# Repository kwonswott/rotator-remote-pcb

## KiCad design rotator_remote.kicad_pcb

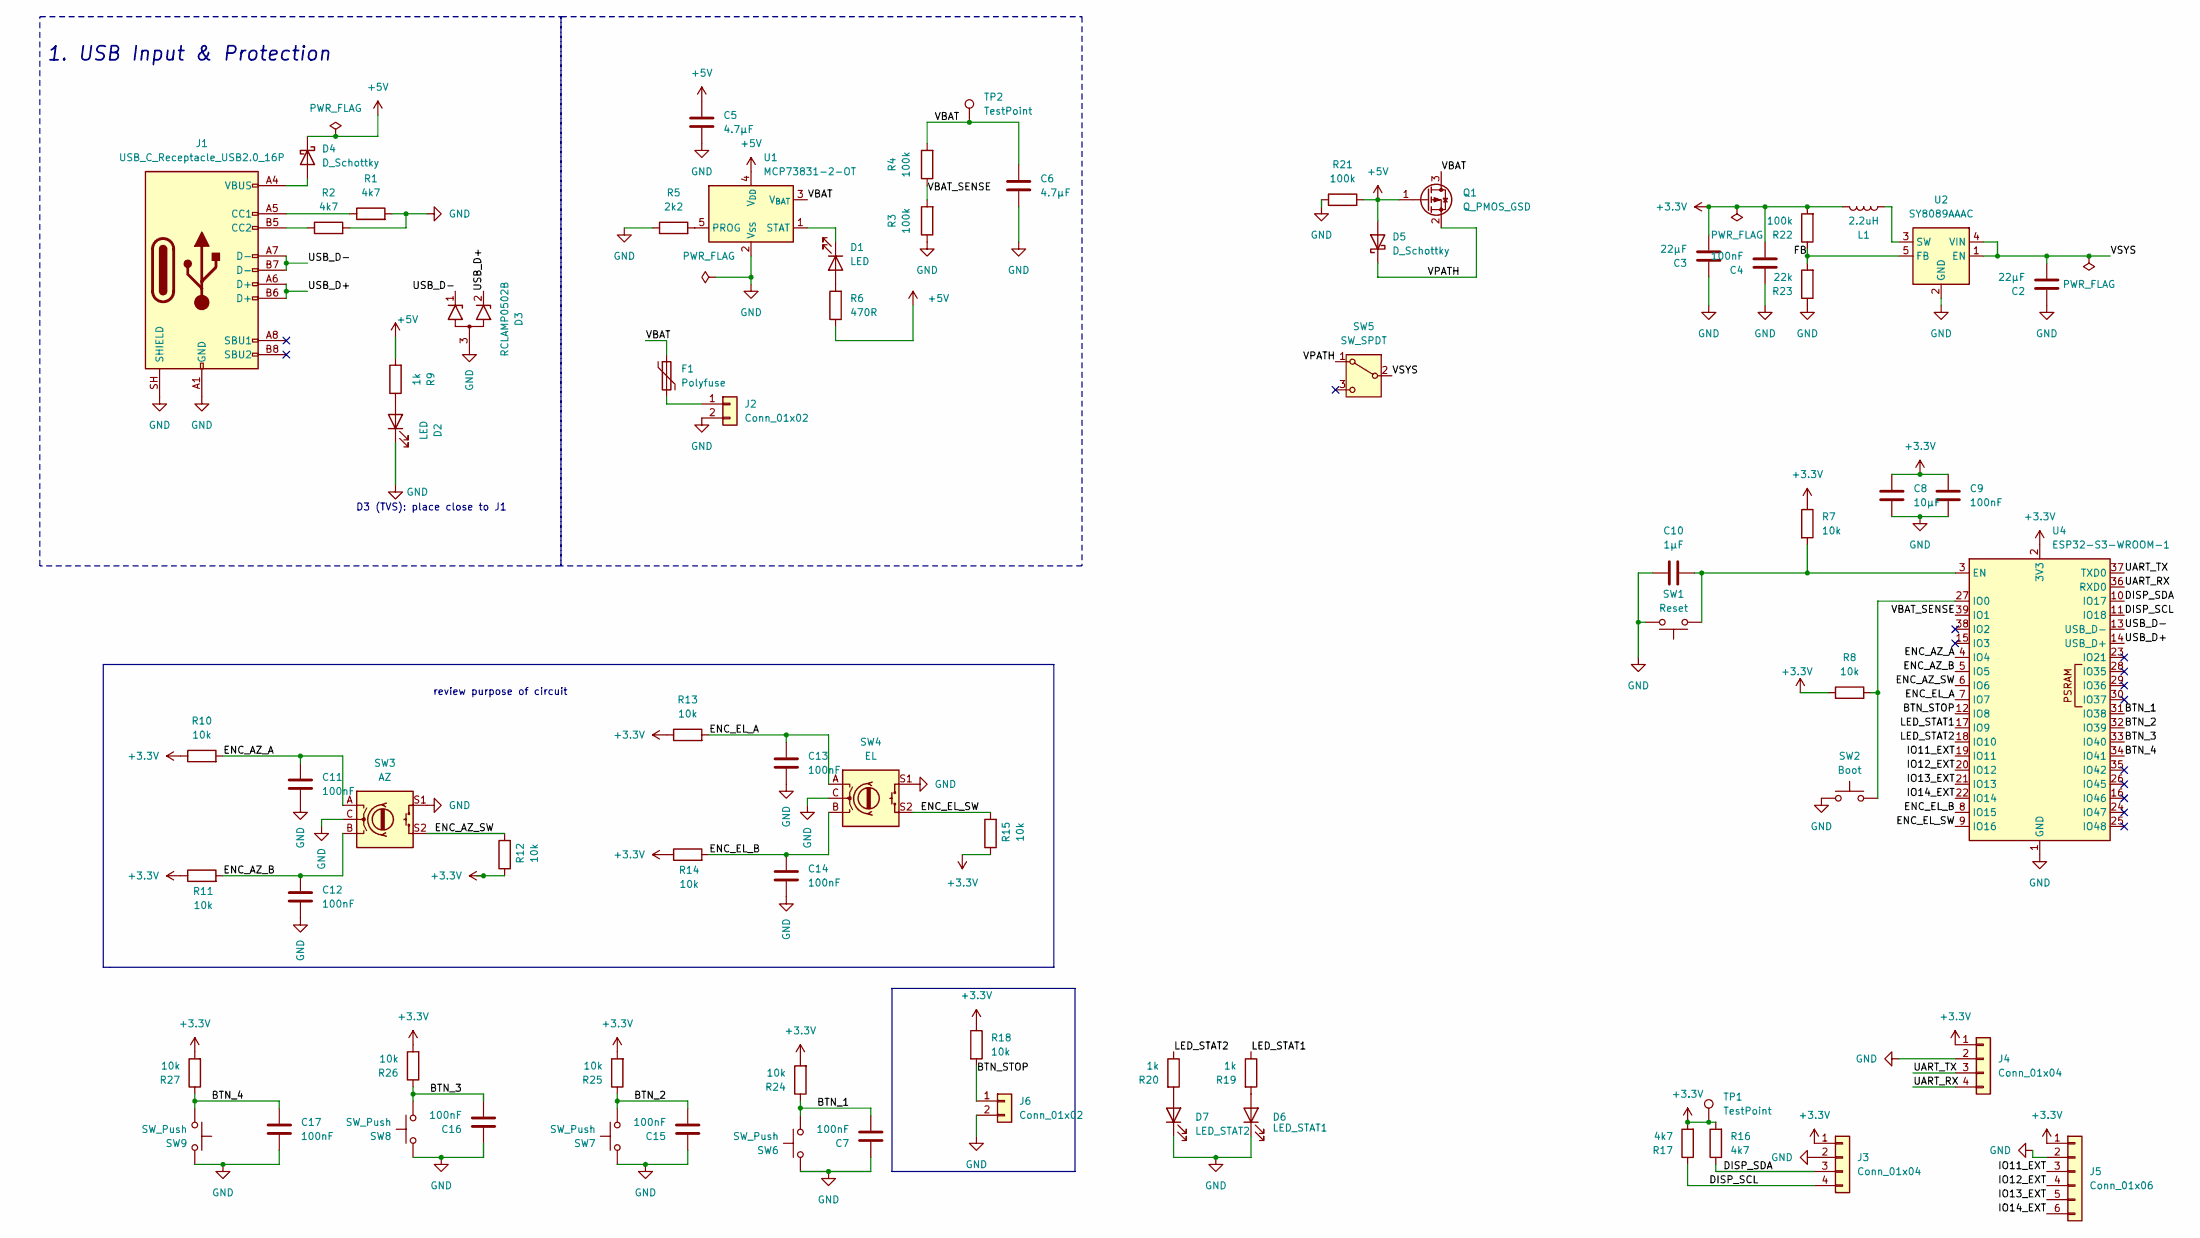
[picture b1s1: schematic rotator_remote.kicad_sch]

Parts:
C2, C3: 22µF; C_1210_3225Metric
C4, C7, C9, C11, C12, C13, C14, C15, C16, C17: 100nF; C_0402_1005Metric
C5, C6: 4.7µF; C_1206_3216Metric
C8: 10µF; C_1206_3216Metric
C10: 1µF; C_0603_1608Metric
D1, D2: LED; LED_0603_1608Metric
D3: RCLAMP0502B; SOT-416
D4, D5: D_Schottky; D_SOD-123
D6: LED_STAT1; LED_0603_1608Metric
D7: LED_STAT2; LED_0603_1608Metric
F1: Polyfuse; Fuse_1206_3216Metric
J1: USB_C_Receptacle_USB2.0_16P; USB_C_Receptacle_HRO_TYPE-C-31-M-12
J2, J6: Conn_01x02; PinHeader_1x02_P2.54mm_Vertical
J3, J4: Conn_01x04; PinHeader_1x04_P2.54mm_Vertical
J5: Conn_01x06; PinHeader_1x06_P2.54mm_Vertical
L1: 2.2uH; L_Changjiang_FXL0630
Q1: Q_PMOS_GSD; SOT-23
R1, R2, R16, R17: 4k7; R_0402_1005Metric
R3, R4, R21, R22: 100k; R_0402_1005Metric
R5: 2k2; R_0402_1005Metric
R6: 470R; R_0402_1005Metric
R7, R8, R10, R11, R12, R13, R14, R15, R18, R24, R25, R26, R27: 10k; R_0402_1005Metric
R9, R19, R20: 1k; R_0402_1005Metric
R23: 22k; R_0402_1005Metric
SW1: Reset; SW_SPST_PTS645Sx43SMTR92
SW2: Boot; SW_SPST_PTS645Sx43SMTR92
SW3: AZ; RotaryEncoder_Alps_EC11E-Switch_Vertical_H20mm
SW4: EL; RotaryEncoder_Alps_EC11E-Switch_Vertical_H20mm
SW5: SW_SPDT; SW_SPDT_PCM12
SW6, SW7, SW8, SW9: SW_Push; SW_PUSH-12mm
TP1, TP2: TestPoint; TestPoint_Pad_D1.5mm
U1: MCP73831-2-OT; SOT-23-5
U2: SY8089AAAC; SOT-23-5
U4: ESP32-S3-WROOM-1

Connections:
+3.3V: C3.2, C4.1, C8.1, C9.1, J3.1, J4.1, J5.1, L1.2, R7.1, R8.1, R10.1, R11.1, R12.1, R13.1, R14.1, R15.1, R16.2, R17.2, R18.1, R22.2, R24.2, R25.2, R26.2, R27.2, TP1.1 (1_1), U4.2 (3V3)
+5V: C5.2, D4.1 (K), D5.2 (A), Q1.1 (G), R6.1, R9.2, R21.2, U1.4 (V_{DD})
/BTN_1: C7.2, R24.1, SW6.2, U4.31 (IO38)
/BTN_2: C15.2, R25.1, SW7.2, U4.32 (IO39)
/BTN_3: C16.2, R26.1, SW8.2, U4.33 (IO40)
/BTN_4: C17.1, R27.1, SW9.1, U4.34 (IO41)
/BTN_STOP: J6.1, R18.2, U4.12 (IO8)
/DISP_SCL: J3.4, R17.1, U4.11 (IO18)
/DISP_SDA: J3.3, R16.1, U4.10 (IO17)
/ENC_AZ_A: C11.1, R10.2, SW3.A, U4.4 (IO4)
/ENC_AZ_B: C12.1, R11.2, SW3.B, U4.5 (IO5)
/ENC_AZ_SW: R12.2, SW3.S2, U4.6 (IO6)
/ENC_EL_A: C13.1, R13.2, SW4.A, U4.7 (IO7)
/ENC_EL_B: C14.1, R14.2, SW4.B, U4.8 (IO15)
/ENC_EL_SW: R15.2, SW4.S2, U4.9 (IO16)
/FB: R22.1, R23.2, U2.5 (FB)
/IO11_EXT: J5.3, U4.19 (IO11)
/IO12_EXT: J5.4, U4.20 (IO12)
/IO13_EXT: J5.5, U4.21 (IO13)
/IO14_EXT: J5.6, U4.22 (IO14)
/LED_STAT1: R19.1, U4.17 (IO9)
/LED_STAT2: R20.1, U4.18 (IO10)
/UART_RX: J4.4, U4.36 (RXD0)
/UART_TX: J4.3, U4.37 (TXD0)
/USB_D+: D3.2 (K2), J1.A6 (D+), J1.B6 (D+), U4.14 (USB_D+)
/USB_D-: D3.1 (K1), J1.A7 (D-), J1.B7 (D-), U4.13 (USB_D-)
/VBAT: C6.1, F1.1, Q1.3 (D), R4.2, TP2.1 (1_1), U1.3 (V_{BAT})
/VBAT_SENSE: R3.2, R4.1, U4.39 (IO1)
/VPATH: D5.1 (K), Q1.2 (S), SW5.1 (A)
/VSYS: C2.2, SW5.2 (B), U2.1 (EN), U2.4 (VIN)
GND: C2.1, C3.1, C4.2, C5.1, C6.2, C7.1, C8.2, C9.2, C10.1, C11.2, C12.2, C13.2, C14.2, C15.1, C16.1, C17.2, D2.1 (K), D3.3 (A), D6.1 (K), D7.1 (K), J1.A1 (GND), J1.A12 (GND), J1.B1 (GND), J1.B12 (GND), J1.SH (SHIELD), J2.2, J3.2, J4.2, J5.2, J6.2, R1.2, R2.2, R3.1, R5.1, R21.1, R23.1, SW1.2, SW2.1, SW3.C, SW3.S1, SW4.C, SW4.S1, SW6.1, SW7.1, SW8.1, SW9.2, U1.2 (V_{SS}), U2.2 (GND), U4.1 (GND), U4.40 (GND), U4.41 (GND)
unnamed: D1.2 (A), R6.2
unnamed: D1.1 (K), U1.1 (STAT)
unnamed: D2.2 (A), R9.1
unnamed: D4.2 (A), J1.A4 (VBUS), J1.A9 (VBUS), J1.B4 (VBUS), J1.B9 (VBUS)
unnamed: D6.2 (A), R19.2
unnamed: D7.2 (A), R20.2
unnamed: J1.A5 (CC1), R1.1
unnamed: J1.B5 (CC2), R2.1
unnamed: F1.2, J2.1
unnamed: R5.2, U1.5 (PROG)
unnamed: L1.1, U2.3 (SW)
unnamed: C10.2, R7.2, SW1.1, U4.3 (EN)
unnamed: R8.2, SW2.2, U4.27 (IO0)

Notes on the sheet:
D3 (TVS): place close to J1
1. USB Input & Protection
review purpose of circuit

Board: 2 copper layers, 77 parts (5 on the bottom side), 44 nets, no tracks yet.

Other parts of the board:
H1, H2, H3, H4: MountingHole_3.2mm_M3
